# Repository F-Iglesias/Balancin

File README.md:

# A hand-made self balancing robot!

It balances itself with a PID control, measuring the angle 

## Third and final prototype

You can see a video of the robot moving [here](https://www.youtube.com/watch?v=WksrDXhgYMs)

### Main board

### Encoders (3D printed and designed by me)

## Second prototype

[Here](https://youtube.com/shorts/iVz-gH_mcks?feature=share) is a video.

For this prototype I designed a simpler encoder, but since it was not able to read the direction in which the wheels rotated, it was useless for its purpose, so I discarded that design.

## First prototype

Sadly I lost all the photos I had, but here are two videos:

[Video 1](https://youtube.com/shorts/Z38a0RHIttk?feature=share)

[Video 2](https://youtube.com/shorts/8MTNevPrN3k?feature=share)

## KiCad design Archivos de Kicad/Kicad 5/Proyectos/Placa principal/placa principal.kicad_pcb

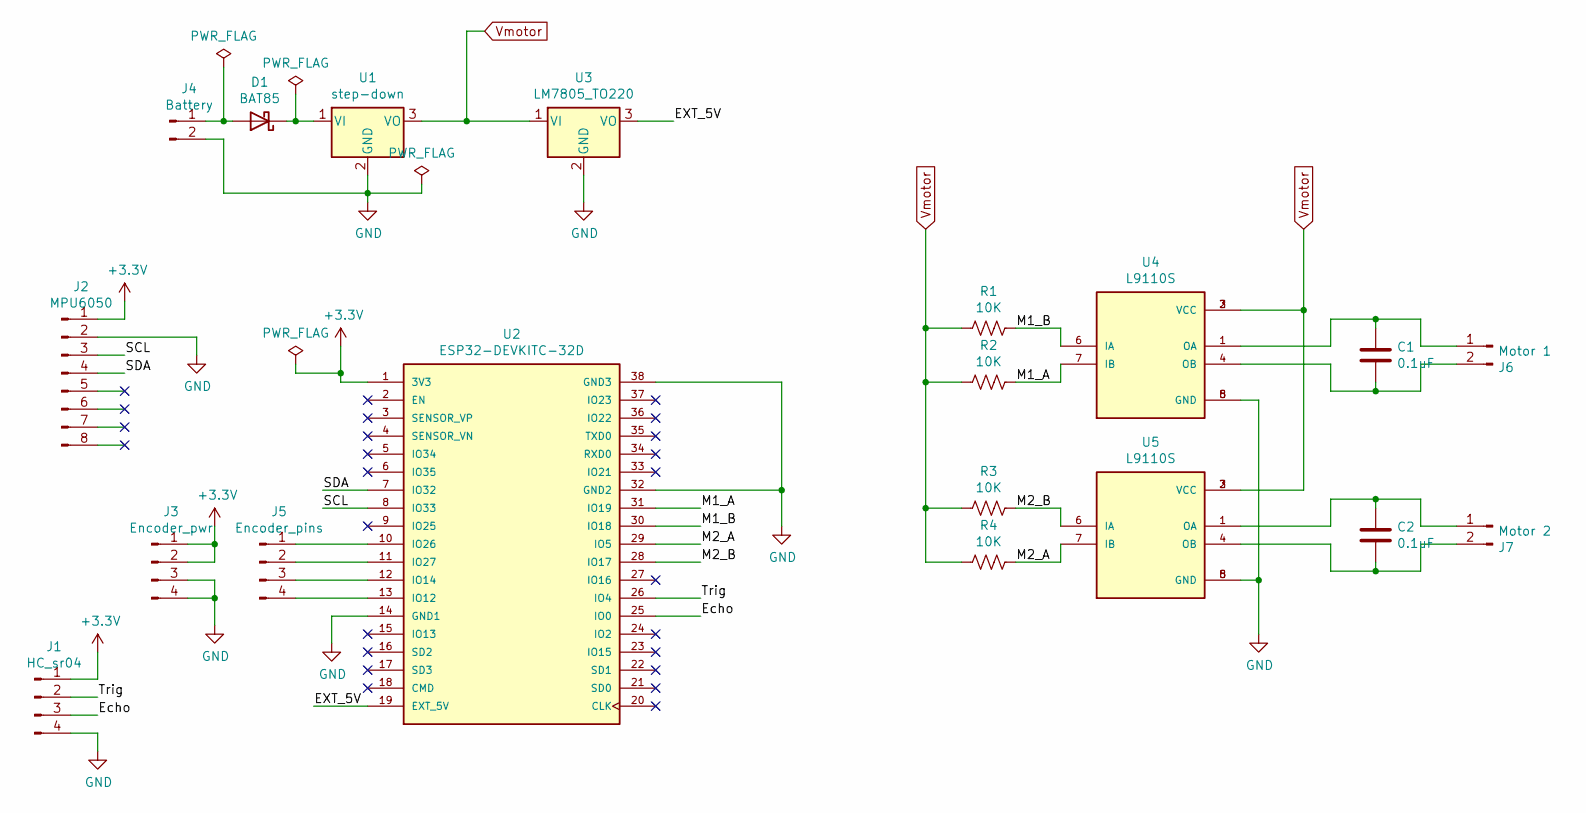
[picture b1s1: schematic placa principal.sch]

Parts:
C1, C2: 0.1uF; C_0805_HandSolder
D1: BAT85
J1: HC_sr04; HC-sr04
J2: MPU6050
J3: Encoder_pwr
J4: Battery; Bornera(5,08mm)
J5: Encoder_pins
J6: Motor 1; Bornera(5,08mm)
J7: Motor 2; Bornera(5,08mm)
R1, R2, R3, R4: 10K; R_0805_HandSolder
U1: step-down; XL4005_Module
U2: ESP32-DEVKITC-32D; MODULE_ESP32-DEVKITC-32D; PARTREV V4
U3: LM7805_TO220; TO-220-3_Vertical
U4, U5: L9110S; L9110s; PARTREV NA

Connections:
+3V3: J1.1, J2.1, J3.1, J3.2, U2.1 (3V3)
/EXT_5V: U2.19 (EXT_5V), U3.3 (VO)
/Echo: J1.3, U2.25 (IO0)
/M1_A: R2.1, U2.31 (IO19), U4.7 (IB)
/M1_B: R1.1, U2.30 (IO18), U4.6 (IA)
/M2_A: R4.1, U2.29 (IO5), U5.7 (IB)
/M2_B: R3.1, U2.28 (IO17), U5.6 (IA)
/SCL: J2.3, U2.8 (IO33)
/SDA: J2.4, U2.7 (IO32)
/Trig: J1.2, U2.26 (IO4)
GND: J1.4, J2.2, J3.3, J3.4, J4.2, U1.2 (GND), U2.14 (GND1), U2.32 (GND2), U2.38 (GND3), U3.2 (GND), U4.5 (GND), U4.8 (GND), U5.5 (GND), U5.8 (GND)
unnamed: C1.1, J6.1, U4.1 (OA)
unnamed: C1.2, J6.2, U4.4 (OB)
unnamed: C2.1, J7.1, U5.1 (OA)
unnamed: C2.2, J7.2, U5.4 (OB)
unnamed: D1.1 (K), U1.1 (VI)
unnamed: D1.2 (A), J4.1
unnamed: J5.1, U2.10 (IO26)
unnamed: J5.2, U2.11 (IO27)
unnamed: J5.3, U2.12 (IO14)
unnamed: J5.4, U2.13 (IO12)
Vmotor: R1.2, R2.2, R3.2, R4.2, U1.3 (VO), U3.1 (VI), U4.2 (VCC), U4.3 (VCC), U5.2 (VCC), U5.3 (VCC)

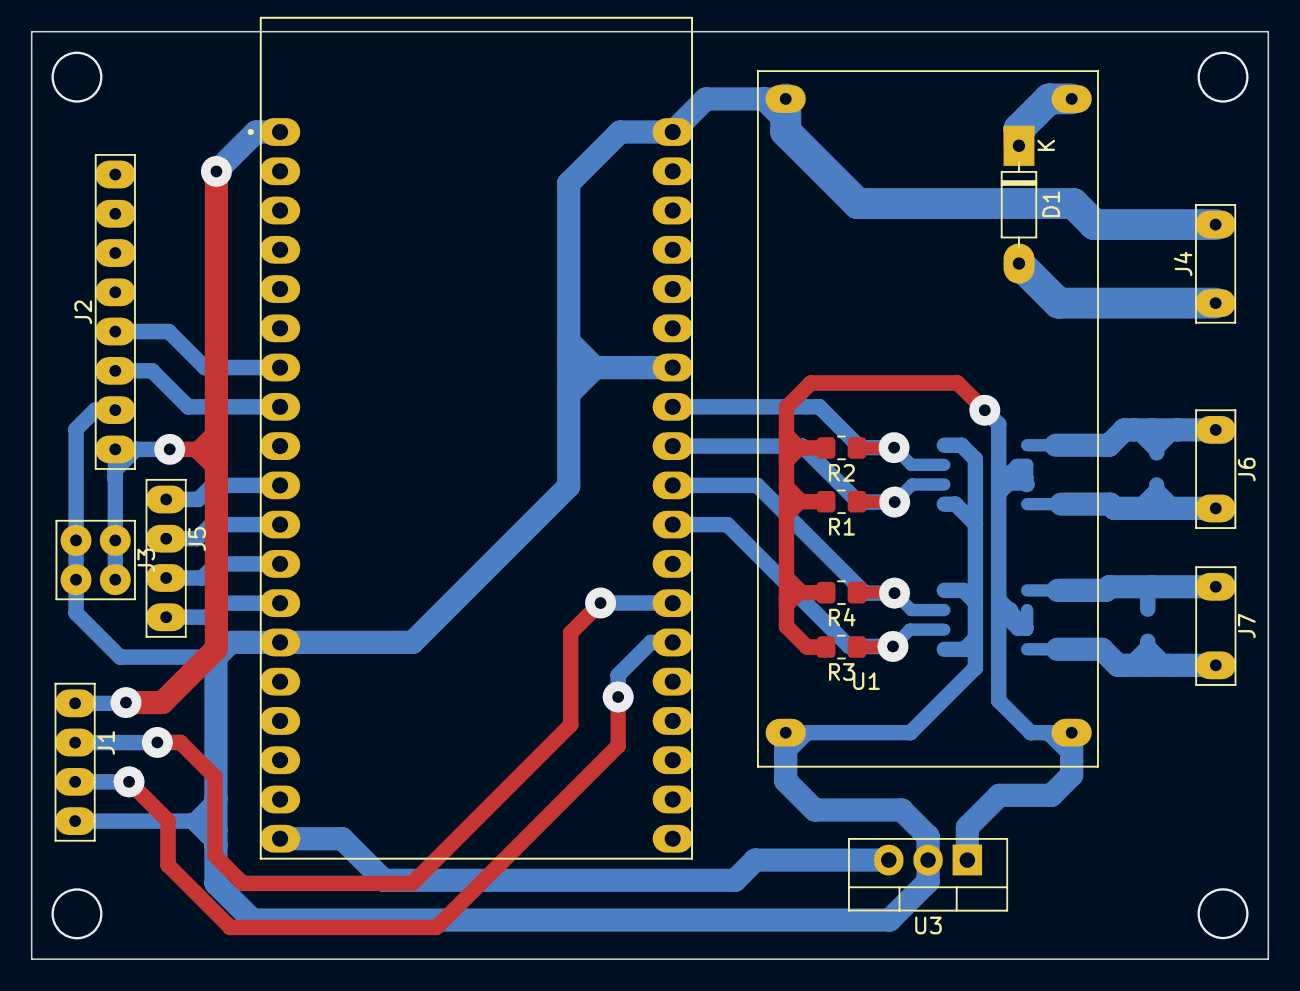
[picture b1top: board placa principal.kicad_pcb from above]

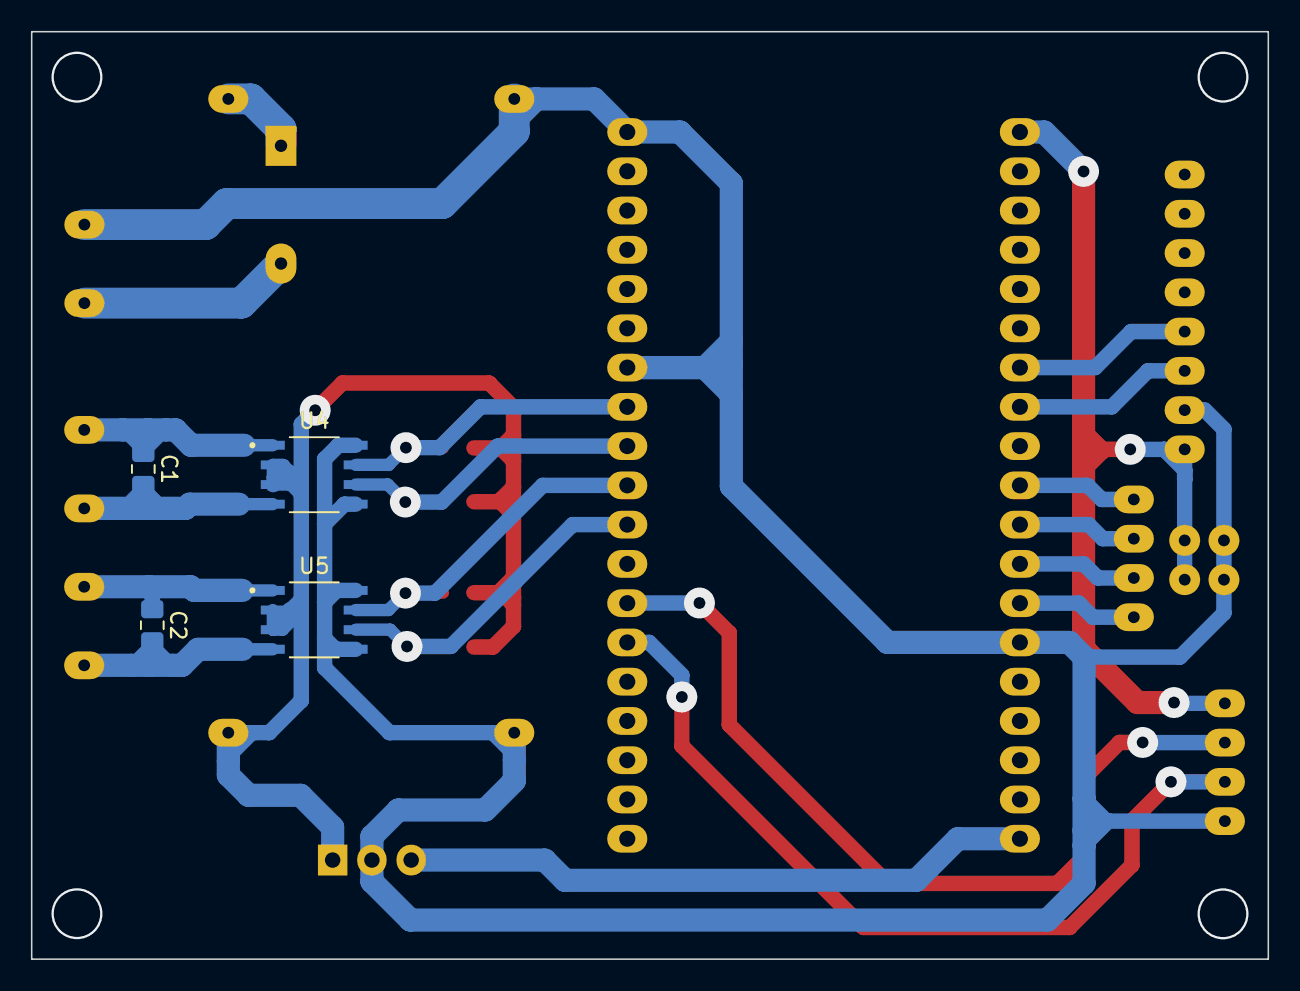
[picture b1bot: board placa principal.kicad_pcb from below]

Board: 2 copper layers, 80.0 x 60.0 mm, 19 parts (4 on the bottom side), 22 nets.

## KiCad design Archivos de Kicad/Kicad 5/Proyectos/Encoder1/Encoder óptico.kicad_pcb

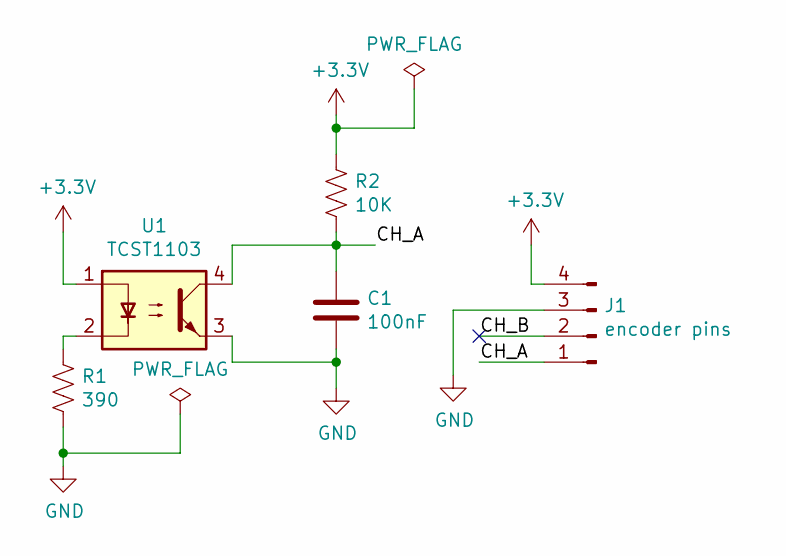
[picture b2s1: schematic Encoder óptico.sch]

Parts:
C1: 100nF; C_0805_2012Metric_Pad1.18x1.45mm_HandSolder
J1: encoder pins; encoder1_pines
R1: 390; R_0805_2012Metric_Pad1.20x1.40mm_HandSolder
R2: 10K; R_0805_2012Metric_Pad1.20x1.40mm_HandSolder
U1: TCST1103

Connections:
+3V3: J1.4, R2.1, U1.1
/CH_A: C1.1, J1.1, R2.2, U1.4
/CH_B: J1.2
GND: C1.2, J1.3, R1.2, U1.3
unnamed: R1.1, U1.2

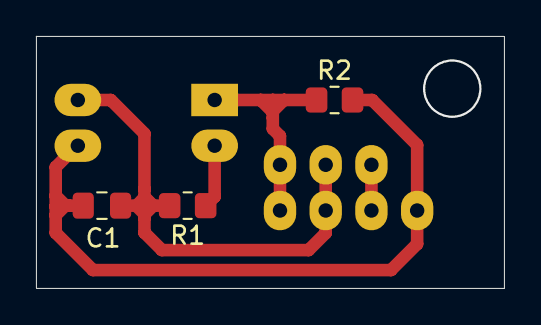
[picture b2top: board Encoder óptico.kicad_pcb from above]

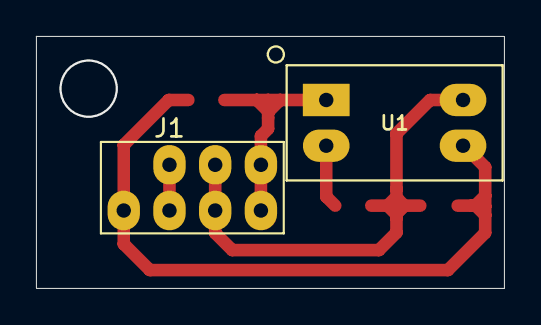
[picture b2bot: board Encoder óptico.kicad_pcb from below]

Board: 2 copper layers, 26.0 x 14.0 mm, 5 parts (2 on the bottom side), 4 nets.
